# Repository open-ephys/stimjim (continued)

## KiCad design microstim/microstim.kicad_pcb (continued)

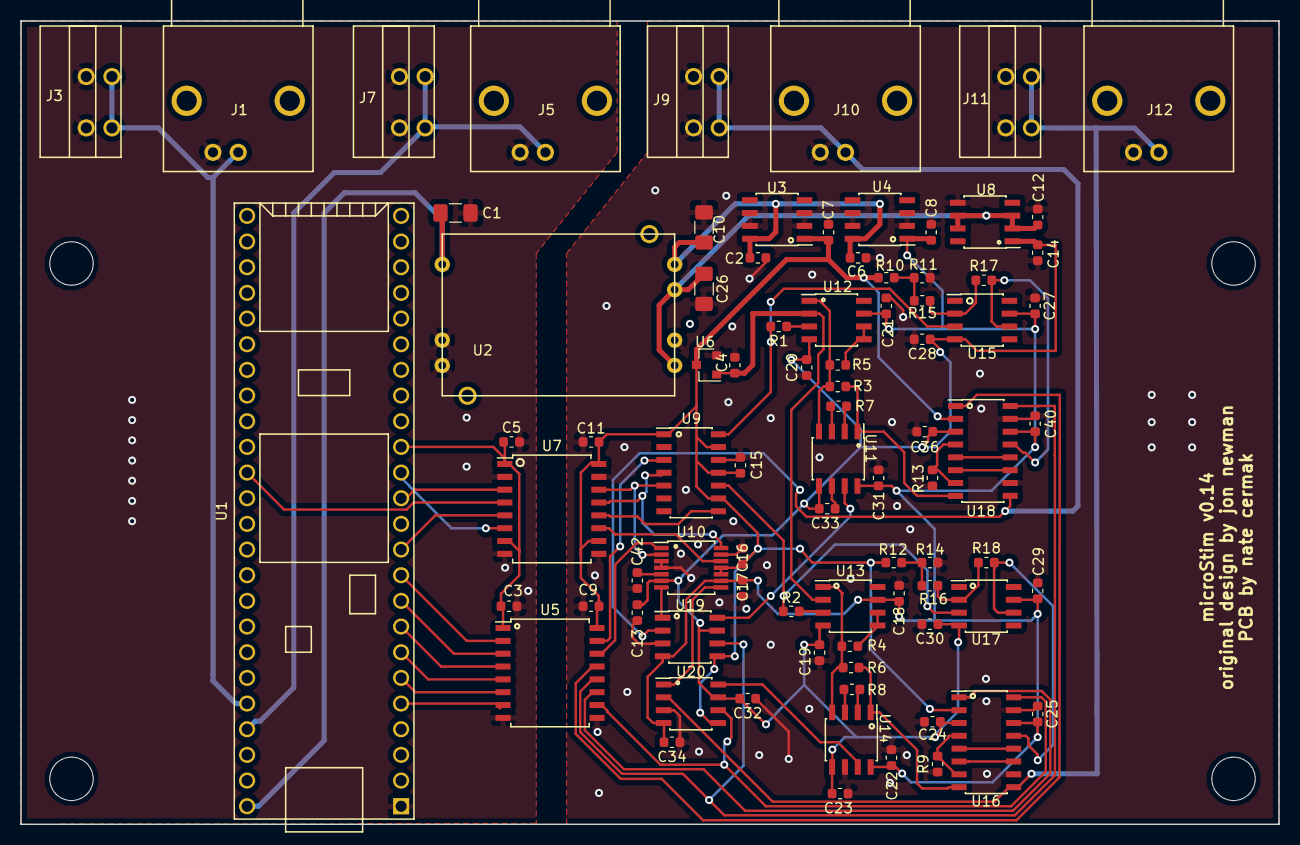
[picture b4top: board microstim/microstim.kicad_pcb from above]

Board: 2 copper layers, 124.5 x 79.5 mm, 87 parts (0 on the bottom side), 65 nets.

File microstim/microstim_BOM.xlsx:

Id | Designator | Package | Quantity | Designation | Supplier and ref | Unit cost | Total cost
1 | U1 | Teensy35_36_noInternalPins | 1 | Teensy3.5 | 1568-1464-ND | 31.25 | 31.25
2 | J12,J1,J10,J5 | 731375003 | 4 | Conn_Coaxial | WM5514-ND | 1.48 | 5.92
3 | C42 | C_0603_1608Metric | 1 | 680nF | 732-7988-1-ND | 0.1 | 0.1
4 | C34,C32,C29,C30,C27,C28,C3,C5,C9,C11,C13,C15,C16,C17,C18,C19,C20,C21,C22,C23,C2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 | C_0603_1608Metric | 26 | 0.1uF | CL10F104ZO8NNNC | 0.038 | 0.988
5 | U19,U20 | SOIC-8_3.9x4.9mm_P1.27mm | 2 | DG419LDY | DG419LDY+-ND | 4.53 | 9.06
6 | C10,C26,C1 | C_1206_3216Metric_Pad1.42x1.75mm_HandSolder | 3 | 10uF | 311-1376-1-ND | 0.4 | 1.2
7 | U17,U15 | SOIC-8_3.9x4.9mm_P1.27mm | 2 | OPA197 | 296-43866-1-ND | 1.6 | 3.2
8 | R15,R16,R9,R13 | R_0603_1608Metric | 4 | 1k | RR08P1.0KDCT-ND | 0.11 | 0.44
9 | R12,R10 | R_0603_1608Metric | 2 | 100 | RR05P100DCT-ND | 0.1 | 0.2
10 | R11,R14 | R_0603_1608Metric | 2 | 180 | RR05P180DCT-ND | 0.1 | 0.2
11 | R17,R18 | R_0603_1608Metric | 2 | 4k | RR05P4.02KDCT-ND | 0.1 | 0.2
12 | U7 | SOIC-16W_7.5x10.3mm_P1.27mm | 1 | ISO7341C | 296-47779-1-ND | 4.32 | 4.32
13 | C6,C2,C7,C8,C12,C14,C4 | C_0603_1608Metric | 7 | 1uF | 1276-1019-1-ND | 0.1 | 0.7
14 | R8,R7 | R_0603_1608Metric | 2 | 1.2k | P20292CT-ND | 0.18 | 0.36
15 | U10 | TSSOP-14_4.4x5mm_P0.65mm | 1 | AD7321 | AD7321BRUZ-REEL7CT-ND | 7.84 | 7.84
16 | U2 | CC3-0512DF-E | 1 | CC3-0512DF-E | 445-2465-ND | 11.21 | 11.21
17 | U3 | SOIC-8_3.9x4.9mm_P1.27mm | 1 | L78L05_SO8 | MC78L05ACDXCT-ND | 0.48 | 0.48
18 | U4 | SOIC-8_3.9x4.9mm_P1.27mm | 1 | L78L12_SO8 | MC78L12ABDGOS-ND | 0.44 | 0.44
19 | U5 | SOIC-16W_7.5x10.3mm_P1.27mm | 1 | ISO7760 | 296-48142-1-ND | 4.44 | 4.44
20 | U8 | SOIC-8_3.9x4.9mm_P1.27mm | 1 | L79L12_SO8 | MC79L12ACDR2GOSCT-ND | 0.41 | 0.41
21 | U9 | SOIC-14_3.9x8.7mm_P1.27mm | 1 | MCP4922 | MCP4922-E/SL-ND | 2.7 | 2.7
22 | R1,R2,R4,R5 | R_0603_1608Metric | 4 | 3k | P3.0KBECT-ND | 0.8 | 3.2
23 | R3,R6 | R_0603_1608Metric | 2 | 250 | P249BLCT-ND | 0.13 | 0.26
24 | U12,U13 | SOIC-8_3.9x4.9mm_P1.27mm | 2 | AD8276 | AD8276ARZ-ND | 2.73 | 5.46
25 | U14,U11 | SOIC-8_3.9x4.9mm_P1.27mm | 2 | INA826 | 296-30238-1-ND | 2.81 | 5.62
26 | U16,U18 | SOIC-16_3.9x9.9mm_P1.27mm | 2 | DG509ACWE | DG509BEY-T1-E3CT-ND | 2.43 | 4.86 | DG409DY-T1-E3CT-ND
27 | U6 | SOT-23 | 1 | AD1582 | AD1582ARTZREEL7CT-ND | 1.76 | 1.76
28 | J3,J7,J9,J11 | 1-2834016-2 _TERM_BLK_2P_SIDE_ENT_2.54MM_PCB | 4 | Screw_Terminal_01x02 | A123829-ND | 1.02 | 4.08
 | Enclosure |  | 1 |  | B5-080BK | 18.71 | 18.71
 | Main board PCB |  | 1
 | Panel PCB |  | 2
 |  |  |  |  |  | Total cost: | 129.608

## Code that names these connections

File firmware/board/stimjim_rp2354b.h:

pico_board_cmake_set(PICO_PLATFORM, rp2350)

#define PICO_RP2350A  0

#define NLDAC_A       43u
#define CS_DAC_A      45u
#define CS_ADC_A      41u
#define OE0_A         38u
#define OE1_A         37u
#define LED_A          2u
#define CHANNEL_IO_A  33u
#define SPI_SCK_A     46u
#define SPI_MOSI_A    47u
#define SPI_MISO_A    44u

#define NLDAC_B       24u
#define CS_DAC_B      21u
#define CS_ADC_B      17u
#define OE0_B         19u
#define OE1_B         18u
#define LED_B          3u
#define CHANNEL_IO_B  34u
#define SPI_SCK_B     22u
#define SPI_MOSI_B    23u
#define SPI_MISO_B    20u

#define GPIO0         10u
#define GPIO1          9u
#define GPIO2          7u
#define GPIO3          6u
#define GPIO4          5u
#define GPIO5          4u
#define GPIO6         13u
#define GPIO7         14u

#define SYNC_A        GPIO6
#define SYNC_B        GPIO7

#define RISING_EDGE_INTERRUPT_BIT(gpio_number, value) ((value) << (4 * ((gpio_number) % 8) + 3))

#define ADC_LEAD_MARGIN_US 2u

#define MICROAMPS_PER_ADC   (20e6f / (1.0f + (49.4f / 1.8f)) / 100.0f / (float)(1 << 13))
#define MILLIVOLTS_PER_ADC  (20e3f / (float)(1 << 13))

#define DAC_FULL_SCALE_V    5.0f
#define R_CURRENT_OHMS      1500.0f
#define V_OUT_GAIN          (1.0f + (10.0f / 5.0f))
#define MAX_MICROAMPS       3333
#define MAX_MILLIVOLTS      15000
#define MAX_MEASURABLE_MILLIVOLTS 10000
#define MICROAMPS_PER_DAC   (2.0f * DAC_FULL_SCALE_V * 1e6f / R_CURRENT_OHMS / (float)(1 << 16))
#define MILLIVOLTS_PER_DAC  (2.0f * DAC_FULL_SCALE_V * 1e3f * V_OUT_GAIN / (float)(1 << 16))

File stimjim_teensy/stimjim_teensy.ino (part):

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#define PT_ARRAY_LENGTH 10
#define MAX_NUM_STAGES 10

#define OE0_0 6
#define OE1_0 5
#define OE0_1 1
#define OE1_1 0
#define CS0_0 9
#define CS1_0 7
#define CS0_1 3
#define CS1_1 2
#define NLDAC_1 4
#define NLDAC_0 10
#define IN0 22
#define IN1 23
#define LED0 21
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  Serial.println("Booting StimJim on Teensy 3.5!");

  Serial.println("Initializing pins...");
  int pins[] = {NLDAC_0, NLDAC_1, CS0_0, CS1_0, CS0_1, CS1_1, OE0_0, OE1_0, OE0_1, OE1_1, LED0, LED1};
  for (int i = 0; i < 12; i++) {
    pinMode(pins[i], OUTPUT);
    digitalWrite(pins[i], HIGH);
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
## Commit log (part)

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2017-07-17 Initial commit
    - Includes ltspice simulations of basic circuit elements
    - Constant current source to 1.2 mA or so, +/-18V railes
    - Voltage compliance monitor
    - Charge offset regulation
2018-08-22 switched to kicad, new circuit design (mostly very similar to old).
2018-09-02 first complete draft of microstim PCB. no errors in layout.
2018-09-02 Added bill of materials.
2018-09-02 updated datasheets
2018-10-03 fixed some op-amps inserted backwards. also had to recommit everything due to OS upgrade and HD backup.
2018-10-13 redesign based on improved howland source at jon newmans suggestion
2018-10-14 added BOM, cleaned up junk files
2018-10-15 replaced LT1167 with INA826 instrument amp. hopefully this wasn't a terrible decision.
2018-10-16 possible an unsaved change to pcb?
2018-11-15 bunch of small fixes to board. havent yet regenerated gerbers. also added beginnings of teensy controller code.
2018-11-19 started cleaning up teensy code
2018-11-21 testing ADC
2018-11-21 still working on adc
2018-11-26 updates to teensy code to enable pulse train
2018-11-26 fixed incorrect comment
2018-12-01 tons of changes - nearly done with pcb at 125x80mm (designed for slotted enclosure). now has 1) voltage output 2) voltage reading on ADC in both voltage output and current output modes. still need to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
2018-12-05 added datasheets for connector and enclosure. updated BOM. probably tons of updates to schematic/layout (cant remember when last commit was). layout/schematic complete - just need double-checking.
2018-12-05 fixed logic bug and added explicit logic table to schematic
2019-01-23 BOM had 0402 resistors, which should have been 0603. now fixed.
2019-01-24 pulse trains now work, still not properly parameterized for voltage. also updated readme, added visual description of pulse train parameterization.
2019-01-24 updated readme.
2019-01-24 teensy control code now sort of working
2019-01-25 updates to readme about building microstim
2019-01-28 major changes to pulse train parameterization and setup in teensy to enable cross-channel synchronization and significantly more flexible pulsetrain design. also updated README
2019-01-29 lots of cleanup of serial printing
2019-01-30 all cleanup. getVoltageOffsets() and getCurrentOffsets() streamlined, now include averaging ADC reads.
2019-02-08 major updates to isolate each output channel.
2019-02-09 making progress on layout... slowly
2019-02-10 finished layout, schematic+pcb pdfs, BOM. need to do panels.
2019-02-11 merged in benchmarking into v3b. changed 3.3v power pin so that design is compatible with teensy 3.1/2 and 3.5/6.
2019-02-11 a few unsaved changes in pcb?
2019-02-16 increased board size to 129x79.5 from 124.5x79.5, changed enclosure to something on digikey rather than newark. also added trigger capability to teensy code
2019-02-25 boatload of updates via jons suggestions. de-isolated grounds via large resistors+capacitors (to prevent static buildup on animal or issues with large discharges). increased resistor values in voltag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
2019-02-25 renamed stuff and forgot to readd it git proj. now added
2019-02-25 fixed dead links in readme due to name change.
2019-02-25 made combined pcb layout (panel+mainpcb), added fab files
2019-02-28 fixed broken link in readme to fab files
2019-03-19 starting to update teensy code for v0.16 pcb
2019-03-20 code now works, but needs a hardware change - CS1_0 should connect to ENABLE1 on ch2 ISO7341, and vice versa
2019-03-21 added LED indicator code
2019-03-21 replaced terrible 24-pin female header (too tight) with a better 24-pin female header in BOM
2019-03-22 1) separated MISO outputs of isolators to separate teensy pins. this required shifting many chip-select and output-enable signals by one pin. 2) added polarity of connectors to panel silk screen. 3) 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
2019-03-22 rounded panel corners per jons suggestion, updated silkscreen to say v0.17.
2019-03-23 somehow benchmarking vi didnt get committed last time. including it now
2019-03-24 updated benchmarker VI to ensure acquisition starts before serial trigger. also updated teensy code so that first pulse has correct delay (not triggered by intervaltimer)
2019-03-24 changed delay timing during pulse, hopefully to remove any remaining pulse width jitter
2019-03-24 regenerated fab files, schematic and layout files, and BOM.
2019-03-26 added photo to README
2019-03-26 fixed broken link to fab files in readme
2019-04-04 fixed bug where ADC always reads output channel 0 during pulse trains
2019-04-04 changed pulse() function so that it doesnt both writing or reading dacs/adcs on channels that aren't set to output anything
2019-04-15 i thought i commmited this with the last commit
2019-04-17 changed pin definitions to match new board (0.17), some documentation and cleanup, got rid of hopefully unnecessary delays. ch0 not working on current board, not sure if it's a software issue.
2019-05-10 changed adc range settings for zeroing out offsets. added serial commands for setting mode and dac amplitude manually.
2019-05-10 updated benchmarking code
2019-05-10 updates to benchmarking analysis
2019-05-12 changed sweep ranges for benchmarking
2019-05-12 fixed leading space in paramStringFile, updated analysis
2019-05-12 changed benchmarking sweep range for amplitude to start at 20mV or uA.
2019-05-12 updated README to match current parameterizion, fixed a dead link to renamed teensy code
2019-05-12 got pulse widths calibrated right.
2019-05-12 updated pulse priority in teensy code to 64 for more reliable timing
2019-05-13 updated photo again
2019-05-14 updates to analysis code
2019-05-28 realized my 5k resistors were actually 5.05k. modified gain multiplier in library and schematic (kicad and pdf) to say 5.05k.
2019-05-28 updates to analysis - pulse time window for calculating amplitude updated.
2019-06-05 switched output channels in stimjim library to be consistent with front panel. (TODO: schematic still inconsistent). Reorganized BOM.
2019-06-05 added figure captions, more references to analysis.
2019-06-05 missed renaming isolated MOSI nets on last try. fixed now.
2019-06-17 minor fixes in draft, mainly to units
2019-06-17 basic documentation to functions in stimjim library
2019-06-20 resized image, take 2
2019-06-30 sped up trigger response in stimjimPulser to 14us. updated photo. replaced many digitalWrites with digitalWriteFast in library. updates to analysis.
2019-07-01 added opa197 datasheet, updated analysis
2019-07-02 separated panels back out, as they can be ordered as 2-layer board
2019-07-02 stimjim class now properly measures ADC offset and accounts for it. also enforced strict camelCase in class methods/fields.
2019-07-02 updated test protocol, increased intervaltimer priority to 24
2019-07-03 removed fill beneath digital isolators
2019-07-03 removed voltage sweep on boot. added way to check adc offsets and re-estimate them.
2019-07-07 minor changes to vias and label layouts on board. submitted this version for ordering.
2019-07-11 updated changelog
2019-07-25 fixed bug where ADC offset estimate could be affected by initial transient on bootup.
2019-08-06 updated schematic in photo figure
2019-08-31 replaced 0.5% resistors in voltage output with 0.1% (updated BOM), changed gain in lib file, added more documentation to stimjimPulser, added manual voltage control mode.
2019-09-02 added licensing stuff (CERN OHL v1.2 for hardware, GPLv3 for software). changed device picture (fig 1) slightly.
2019-09-02 updated PCB silkscreen to include URL and license. regenerated gerbers.
2019-09-02 removed unused spice dir, organized images into new images folder
2019-10-24 actually now fixed figure schematic!
2019-11-01 push-terminal connectors J6 and J8 somehow missing from BOM - fixed!
2019-11-06 fixed places in README that said ms instead of us, and a string overflow error when printing offsets (thank you Tom Earnest for noting both issues).
2019-12-03 added files for SeeedStudio assembly order. Also major updates to README (including details about SeeedStudio assembly, mostly courtesy of Vincent Prevosto
2019-12-03 more markdown fixes in readme.
2019-12-03 added pcb.pdf to stimjim_SeeedStudioAssembly_PickAndPlace.zip
2019-12-03 readme markdown - wrong heading size.
2020-06-14 updated 78L05 regulator to replace obsolete part
2020-10-03 updated line endings to all be consistent with arduino Serial.println (\r\n, not just \n)
2020-10-05 updated to include internal pulsetrain parameter class and allow storing/running multiple (100) pulsetrains.
2020-10-07 in case of a single-pulse pulsetrain, fixed bug to ensure the LED comes on and the Serial prints before the first pulse is initiated!
2020-10-10 added serial command to stop pulse train (T-1 or U-1). GUI is now more or less working.
2020-10-18 added assembly notes for Teensy
2020-10-18 updated kicad design to meet seeedstudio DFM requirements: (1) fixed DC/DC converter footprint and hole size (2) fixed through-hole size of GPIO 2x8 pin header footprint
2020-10-18 added requirements.txt for gui
2020-10-22 updated serial ports to refresh only when disconnected
2020-10-22 minor gui sizing updates
2023-11-17 Merged in nc-update-to-kicad7 (pull request #3)
    Update PCB design to kicad 7
    * migrate to kicad7
    * remove empty.kicad_wks; fix sheet size and add authors and version to page
    * migrate libraries to new format; fix incorrectly rescued symbols (+3.3V power flag and L78L05-SO8 regulator)
    * slowly fixing all ERC errors; down to 3
    * fix ina826 symbol (again). down to 0 ERC errors; 56 warnings
2023-11-17 Merged in nc-move-channels-to-subsheet (pull request #4)
    Move channel schematic to subsheet, make two instances of it. Fix the ERC and DRC errors I made.
2024-05-31 Small changes to library and pulser code
    - Use GPIO 10 and 11 to indicate stim active on channels 0 and 1
    respectively
    - Check validity of DAC codes when using the A and V commands
    - Document the V command
2024-08-21 Trigger channels can mark stimuli in stimjimPulser
    - The "input" 0 and 1 BNCs on the front panel now default to outputs
    that can mark stimulus times with a digital signal
    - The can be set as inputs that trigger stimului using the R command
    - Fix formatting
2024-11-04 Clear startup message in StimJimBIST - When first plugged in, StimJim sends statup messages that need to be cleared by the BIST before the test starts
2025-04-09 Improve R command docs a bit
    - Add better messages to serial output when R is changed
2025-12-06 Replace teensy with RP235xB
2025-12-14 filipe feedback
2026-01-17 fix curve in silkscreen
2026-01-17 Align trigger labels
    They were like 0.15mm misaligned on the y-axis
2026-01-21 Divide panels into panel-back and panel-front
    - I would rather not put them on the same PCB separated by v-cuts or
    mouse bites since the milling quality matters for panels
2026-03-18 pulse timings on core1
2026-03-23 improve pulse timings
2026-04-08 fix calibrations
2026-04-08 Update notes
2026-04-14 Various bug fixes and simplifying refactors
2026-05-14 Fix pulse train jitter
    Also minor refactors
2026-05-15 Reduce latency between trigger and stimulus delivery
2026-05-27 Replace amplifiers
    - INA826 -> AD8421
    - AMP03 -> LT1995 w/ op-amp in feedback circuit
    - Also:
    - update to kicad v10
    - utilize multi-channel layout feature
    - update calculations on schematic
2026-05-28 fix panel outline
    Remove the finer features that might not
    adhere to best practices for PCB DFM
2026-06-05 handle all mux interactions in core1
2026-06-05 remove unnecessary state and make new function for what happens after ADC is read
2026-06-05 add firmware design description
2026-06-08 tolerance resistors
2026-06-18 blocking stimulus delivery
